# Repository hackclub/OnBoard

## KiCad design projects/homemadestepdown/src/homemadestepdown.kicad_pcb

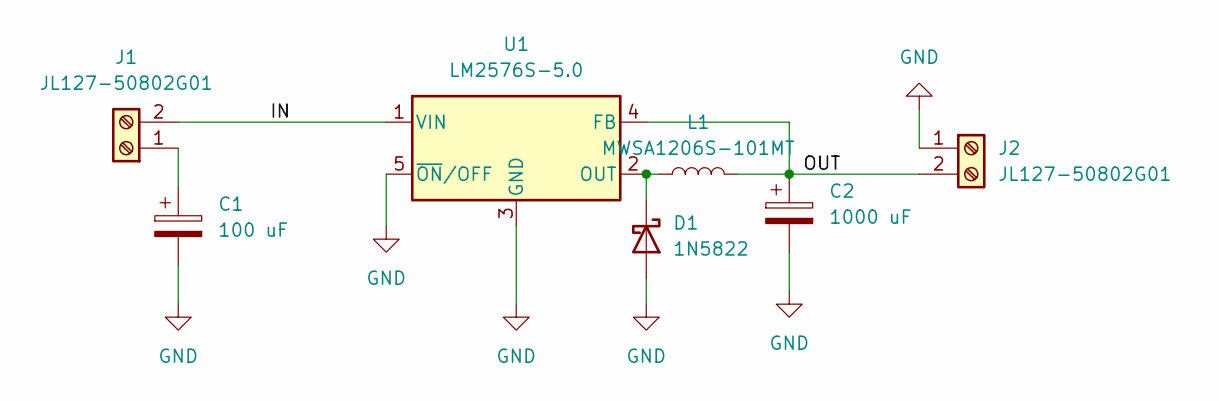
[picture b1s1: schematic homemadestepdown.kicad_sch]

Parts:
C1: 100 uF; CAP-SMD_BD8.0-L8.3-W8.3-FD; LCSC Part # C116241
C2: 1000 uF; CAP-TH_BD8.0-P3.50-D0.6-FD; LCSC Part # C311638
D1: 1N5822; D_DO-201AD_P15.24mm_Horizontal; LCSC Part # C2476
J1, J2: JL127-50802G01; CONN-TH_2P-P5.08_JL127-50802G01; LCSC Part # C409161
L1: MWSA1206S-101MT; IND-SMD_L13.4-W12.6; LCSC Part # C408533
U1: LM2576S-5.0; TO-263-5_TabPin3; LCSC Part # C2920854

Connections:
/IN: J1.2, U1.1 (VIN)
/OUT: C2.1, J2.2, L1.2, U1.4 (FB)
GND: C1.2, C2.2, D1.2 (A), J2.1, U1.3 (GND), U1.5 (~ON/OFF)
unnamed: D1.1 (K), L1.1, U1.2 (OUT)
unnamed: C1.1, J1.1

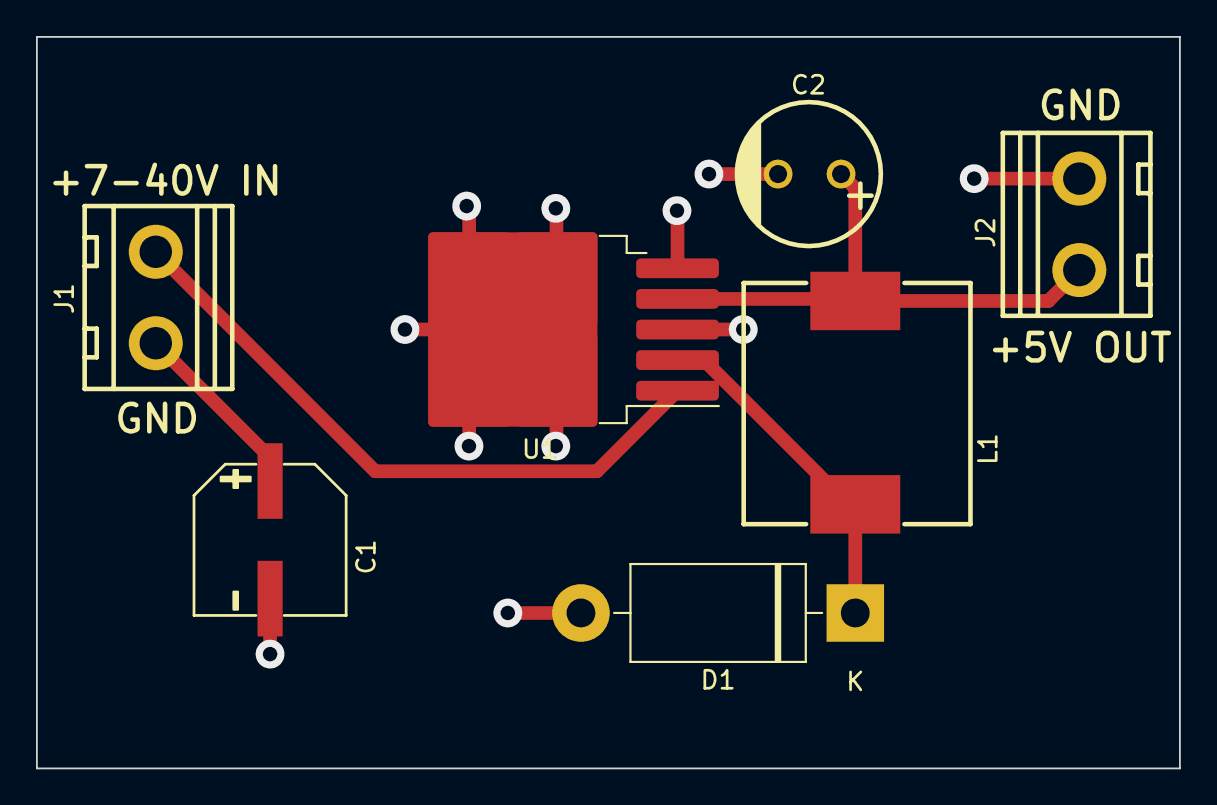
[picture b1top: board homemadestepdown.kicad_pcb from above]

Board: 2 copper layers, 63.5 x 40.6 mm, 7 parts (0 on the bottom side), 5 nets.

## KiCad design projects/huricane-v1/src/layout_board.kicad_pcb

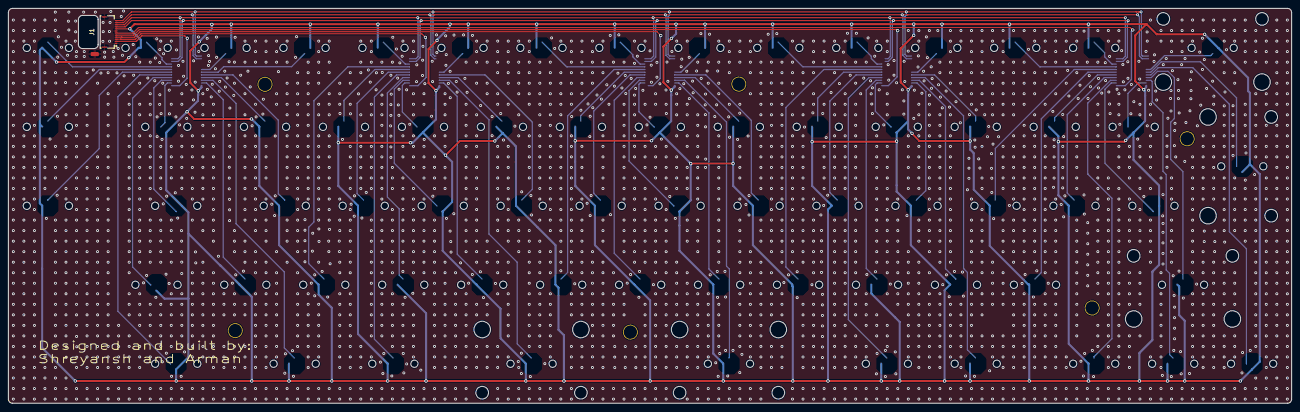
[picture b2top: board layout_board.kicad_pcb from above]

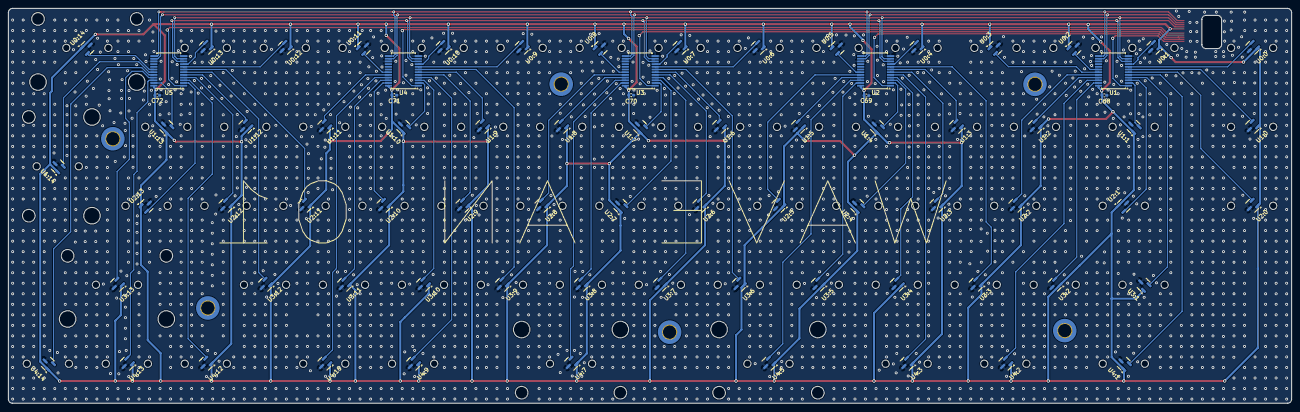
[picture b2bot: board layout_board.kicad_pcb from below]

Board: 2 copper layers, 309.6 x 95.2 mm, 78 parts (77 on the bottom side), 78 nets.

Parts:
C68, C69, C70, C71, C72: 100n; C_0402_1005Metric_Pad0.74x0.62mm_HandSolder
J1: HC-FPC-05-10-12RLTAG; FPC-SMD_12P-P0.50_HCTL_HC-FPC-05-10-12RLTAG
U0:0, U0:1, U0:2, U0:3, U0:4, U0:5, U0:6, U0:7, U0:8, U0:9, U0:10, U0:11, U0:12, U0:13, U0:14, U1:0, U1:1, U1:2, U1:3, U1:4, U1:5, U1:6, U1:7, U1:8, U1:9, U1:10, U1:11, U1:12, U1:13, U1:14, U2:0, U2:1, U2:2, U2:3, U2:4, U2:5, U2:6, U2:7, U2:8, U2:9, U2:10, U2:11, U2:12, U2:13, U3:1, U3:2, U3:3, U3:4, U3:5, U3:6, U3:7, U3:8, U3:9, U3:10, U3:11, U3:12, U3:13, U4:1, U4:2, U4:3, U4:5, U4:7, U4:9, U4:10, U4:12, U4:13, U4:14: GH39FKSW; SOT-23
U1, U2, U3, U4, U5: CD4067BPWR; SSOP-24_5.3x8.2mm_P0.65mm

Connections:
+3.3VA: C68.1, C69.1, C70.1, C71.1, C72.1, J1.8, U0:0.1 (VDD), U0:1.1 (VDD), U0:2.1 (VDD), U0:3.1 (VDD), U0:4.1 (VDD), U0:5.1 (VDD), U0:6.1 (VDD), U0:7.1 (VDD), U0:8.1 (VDD), U0:9.1 (VDD), U0:10.1 (VDD), U0:11.1 (VDD), U0:12.1 (VDD), U0:13.1 (VDD), U0:14.1 (VDD), U1.24 (VDD), U1:0.1 (VDD), U1:1.1 (VDD), U1:2.1 (VDD), U1:3.1 (VDD), U1:4.1 (VDD), U1:5.1 (VDD), U1:6.1 (VDD), U1:7.1 (VDD), U1:8.1 (VDD), U1:9.1 (VDD), U1:10.1 (VDD), U1:11.1 (VDD), U1:12.1 (VDD), U1:13.1 (VDD), U1:14.1 (VDD), U2.24 (VDD), U2:0.1 (VDD), U2:1.1 (VDD), U2:2.1 (VDD), U2:3.1 (VDD), U2:4.1 (VDD), U2:5.1 (VDD), U2:6.1 (VDD), U2:7.1 (VDD), U2:8.1 (VDD), U2:9.1 (VDD), U2:10.1 (VDD), U2:11.1 (VDD), U2:12.1 (VDD), U2:13.1 (VDD), U3.24 (VDD), U3:1.1 (VDD), U3:2.1 (VDD), U3:3.1 (VDD), U3:4.1 (VDD), U3:5.1 (VDD), U3:6.1 (VDD), U3:7.1 (VDD), U3:8.1 (VDD), U3:9.1 (VDD), U3:10.1 (VDD), U3:11.1 (VDD), U3:12.1 (VDD), U3:13.1 (VDD), U4.24 (VDD), U4:1.1 (VDD), U4:2.1 (VDD), U4:3.1 (VDD), U4:5.1 (VDD), U4:7.1 (VDD), U4:9.1 (VDD), U4:10.1 (VDD), U4:12.1 (VDD), U4:13.1 (VDD), U4:14.1 (VDD), U5.24 (VDD)
/ADC0: J1.2, U1.1 (COMMONOUT/IN)
/ADC1: J1.3, U2.1 (COMMONOUT/IN)
/ADC2: J1.4, U3.1 (COMMONOUT/IN)
/ADC3: J1.5, U4.1 (COMMONOUT/IN)
/ADC4: J1.6, U5.1 (COMMONOUT/IN)
/AMUX0:0: U0:1.2 (VOUT), U1.9 (0)
/AMUX0:1: U0:0.2 (VOUT), U1.8 (1)
/AMUX0:2: U1.7 (2), U1:0.2 (VOUT)
/AMUX0:3: U1.6 (3), U2:0.2 (VOUT)
/AMUX0:4: U1.5 (4), U4:1.2 (VOUT)
/AMUX0:5: U1.4 (5), U3:1.2 (VOUT)
/AMUX0:6: U1.3 (6), U2:1.2 (VOUT)
/AMUX0:7: U1.2 (7), U1:1.2 (VOUT)
/AMUX0:8: U1.23 (8), U3:2.2 (VOUT)
/AMUX0:9: U1.22 (9), U4:2.2 (VOUT)
/AMUX0:10: U1.21 (10), U1:2.2 (VOUT)
/AMUX0:11: U1.20 (11), U2:2.2 (VOUT)
/AMUX0:12: U0:3.2 (VOUT), U1.19 (12)
/AMUX0:13: U0:2.2 (VOUT), U1.18 (13)
/AMUX1:0: U0:4.2 (VOUT), U2.9 (0)
/AMUX1:1: U2.8 (1), U3:3.2 (VOUT)
/AMUX1:2: U1:3.2 (VOUT), U2.7 (2)
/AMUX1:3: U2.6 (3), U2:3.2 (VOUT)
/AMUX1:4: U2.5 (4), U4:3.2 (VOUT)
/AMUX1:5: U2.4 (5), U3:4.2 (VOUT)
/AMUX1:6: U2.3 (6), U2:4.2 (VOUT)
/AMUX1:7: U1:4.2 (VOUT), U2.2 (7)
/AMUX1:8: U2.23 (8), U3:5.2 (VOUT)
/AMUX1:9: U2.22 (9), U4:5.2 (VOUT)
/AMUX1:10: U1:5.2 (VOUT), U2.21 (10)
/AMUX1:11: U2.20 (11), U2:5.2 (VOUT)
/AMUX1:12: U0:5.2 (VOUT), U2.19 (12)
/AMUX2:0: U0:7.2 (VOUT), U3.9 (0)
/AMUX2:1: U0:6.2 (VOUT), U3.8 (1)
/AMUX2:2: U3.7 (2), U3:6.2 (VOUT)
/AMUX2:3: U1:6.2 (VOUT), U3.6 (3)
/AMUX2:4: U2:6.2 (VOUT), U3.5 (4)
/AMUX2:5: U3.4 (5), U3:7.2 (VOUT)
/AMUX2:6: U2:7.2 (VOUT), U3.3 (6)
/AMUX2:7: U1:7.2 (VOUT), U3.2 (7)
/AMUX2:8: U3.23 (8), U3:8.2 (VOUT)
/AMUX2:9: U3.22 (9), U4:7.2 (VOUT)
/AMUX2:10: U1:8.2 (VOUT), U3.21 (10)
/AMUX2:11: U2:8.2 (VOUT), U3.20 (11)
/AMUX2:12: U0:8.2 (VOUT), U3.19 (12)
/AMUX3:0: U0:10.2 (VOUT), U4.9 (0)
/AMUX3:1: U0:9.2 (VOUT), U4.8 (1)
/AMUX3:2: U3:9.2 (VOUT), U4.7 (2)
/AMUX3:3: U1:9.2 (VOUT), U4.6 (3)
/AMUX3:4: U2:9.2 (VOUT), U4.5 (4)
/AMUX3:5: U4.4 (5), U4:9.2 (VOUT)
/AMUX3:6: U3:10.2 (VOUT), U4.3 (6)
/AMUX3:7: U1:10.2 (VOUT), U4.2 (7)
/AMUX3:8: U2:10.2 (VOUT), U4.23 (8)
/AMUX3:9: U3:11.2 (VOUT), U4.22 (9)
/AMUX3:10: U4.21 (10), U4:10.2 (VOUT)
/AMUX3:11: U1:11.2 (VOUT), U4.20 (11)
/AMUX3:12: U0:11.2 (VOUT), U4.19 (12)
/AMUX4:0: U0:13.2 (VOUT), U5.9 (0)
/AMUX4:1: U0:12.2 (VOUT), U5.8 (1)
/AMUX4:2: U2:11.2 (VOUT), U5.7 (2)
/AMUX4:3: U3:12.2 (VOUT), U5.6 (3)
/AMUX4:4: U1:12.2 (VOUT), U5.5 (4)
/AMUX4:5: U2:12.2 (VOUT), U5.4 (5)
/AMUX4:6: U4:12.2 (VOUT), U5.3 (6)
/AMUX4:7: U2:13.2 (VOUT), U5.2 (7)
/AMUX4:8: U1:13.2 (VOUT), U5.23 (8)
/AMUX4:9: U4:13.2 (VOUT), U5.22 (9)
/AMUX4:10: U3:13.2 (VOUT), U5.21 (10)
/AMUX4:11: U4:14.2 (VOUT), U5.20 (11)
/AMUX4:12: U1:14.2 (VOUT), U5.19 (12)
/AMUX4:13: U0:14.2 (VOUT), U5.18 (13)
/SELECT0: J1.9, U1.10 (A), U2.10 (A), U3.10 (A), U4.10 (A), U5.10 (A)
/SELECT1: J1.10, U1.11 (B), U2.11 (B), U3.11 (B), U4.11 (B), U5.11 (B)
/SELECT2: J1.11, U1.14 (C), U2.14 (C), U3.14 (C), U4.14 (C), U5.14 (C)
/SELECT3: J1.12, U1.13 (D), U2.13 (D), U3.13 (D), U4.13 (D), U5.13 (D)
GND: C68.2, C69.2, C70.2, C71.2, C72.2, J1.1, J1.7, J1.13, J1.14, U0:0.3 (GND), U0:1.3 (GND), U0:2.3 (GND), U0:3.3 (GND), U0:4.3 (GND), U0:5.3 (GND), U0:6.3 (GND), U0:7.3 (GND), U0:8.3 (GND), U0:9.3 (GND), U0:10.3 (GND), U0:11.3 (GND), U0:12.3 (GND), U0:13.3 (GND), U0:14.3 (GND), U1.12 (VSS), U1.15 (INHIBT), U1:0.3 (GND), U1:1.3 (GND), U1:2.3 (GND), U1:3.3 (GND), U1:4.3 (GND), U1:5.3 (GND), U1:6.3 (GND), U1:7.3 (GND), U1:8.3 (GND), U1:9.3 (GND), U1:10.3 (GND), U1:11.3 (GND), U1:12.3 (GND), U1:13.3 (GND), U1:14.3 (GND), U2.12 (VSS), U2.15 (INHIBT), U2:0.3 (GND), U2:1.3 (GND), U2:2.3 (GND), U2:3.3 (GND), U2:4.3 (GND), U2:5.3 (GND), U2:6.3 (GND), U2:7.3 (GND), U2:8.3 (GND), U2:9.3 (GND), U2:10.3 (GND), U2:11.3 (GND), U2:12.3 (GND), U2:13.3 (GND), U3.12 (VSS), U3.15 (INHIBT), U3:1.3 (GND), U3:2.3 (GND), U3:3.3 (GND), U3:4.3 (GND), U3:5.3 (GND), U3:6.3 (GND), U3:7.3 (GND), U3:8.3 (GND), U3:9.3 (GND), U3:10.3 (GND), U3:11.3 (GND), U3:12.3 (GND), U3:13.3 (GND), U4.12 (VSS), U4.15 (INHIBT), U4:1.3 (GND), U4:2.3 (GND), U4:3.3 (GND), U4:5.3 (GND), U4:7.3 (GND), U4:9.3 (GND), U4:10.3 (GND), U4:12.3 (GND), U4:13.3 (GND), U4:14.3 (GND), U5.12 (VSS), U5.15 (INHIBT)

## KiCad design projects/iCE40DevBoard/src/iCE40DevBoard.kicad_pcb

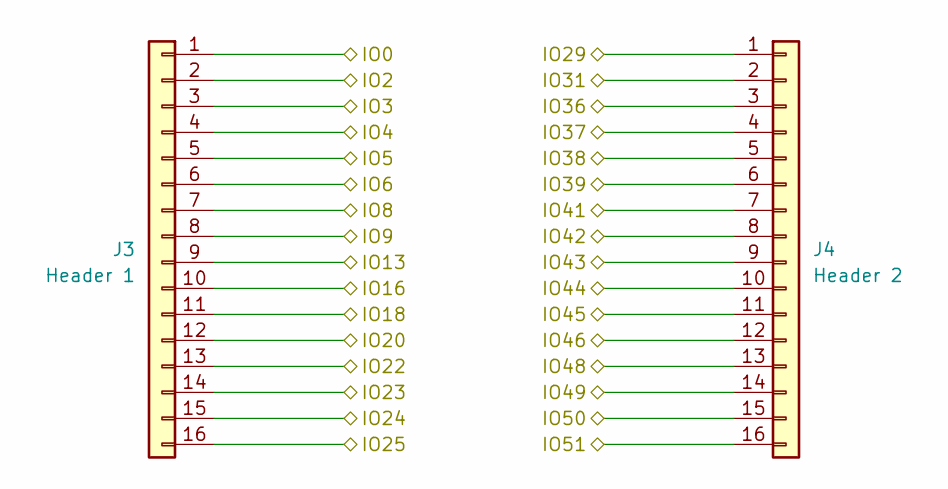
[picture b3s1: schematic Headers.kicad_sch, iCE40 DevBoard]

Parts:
J3: Header 1; PinHeader_1x16_P2.54mm_Vertical
J4: Header 2; PinHeader_1x16_P2.54mm_Vertical

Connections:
/FPGA/IO0: J3.1; also elsewhere on the board
/FPGA/IO2: J3.2; also elsewhere on the board
/FPGA/IO3: J3.3; also elsewhere on the board
/FPGA/IO4: J3.4; also elsewhere on the board
/FPGA/IO5: J3.5; also elsewhere on the board
/FPGA/IO6: J3.6; also elsewhere on the board
/FPGA/IO8: J3.7; also elsewhere on the board
/FPGA/IO9: J3.8; also elsewhere on the board
/FPGA/IO13: J3.9; also elsewhere on the board
/FPGA/IO16: J3.10; also elsewhere on the board
/FPGA/IO18: J3.11; also elsewhere on the board
/FPGA/IO20: J3.12; also elsewhere on the board
/FPGA/IO22: J3.13; also elsewhere on the board
/FPGA/IO23: J3.14; also elsewhere on the board
/FPGA/IO24: J3.15; also elsewhere on the board
/FPGA/IO25: J3.16; also elsewhere on the board
/FPGA/IO29: J4.1; also elsewhere on the board
/FPGA/IO31: J4.2; also elsewhere on the board
/FPGA/IO36: J4.3; also elsewhere on the board
/FPGA/IO37: J4.4; also elsewhere on the board
/FPGA/IO38: J4.5; also elsewhere on the board
/FPGA/IO39: J4.6; also elsewhere on the board
/FPGA/IO41: J4.7; also elsewhere on the board
/FPGA/IO42: J4.8; also elsewhere on the board
/FPGA/IO43: J4.9; also elsewhere on the board
/FPGA/IO44: J4.10; also elsewhere on the board
/FPGA/IO45: J4.11; also elsewhere on the board
/FPGA/IO46: J4.12; also elsewhere on the board
/FPGA/IO48: J4.13; also elsewhere on the board
/FPGA/IO49: J4.14; also elsewhere on the board
/FPGA/IO50: J4.15; also elsewhere on the board
/FPGA/IO51: J4.16; also elsewhere on the board

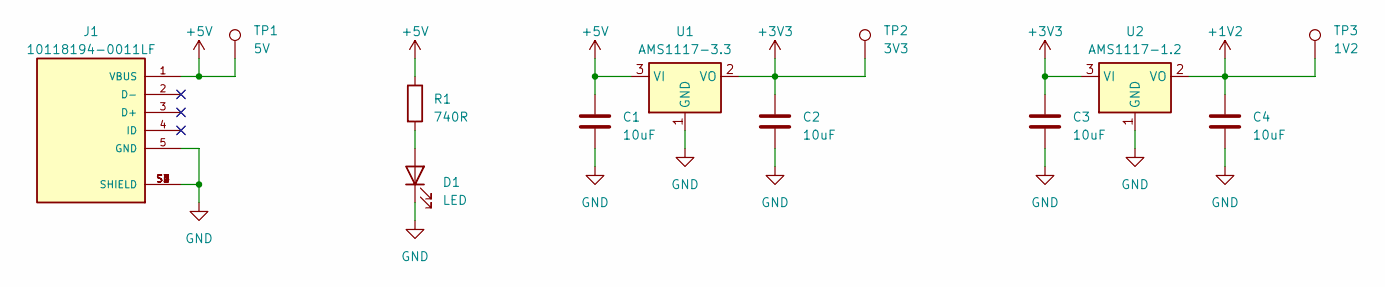
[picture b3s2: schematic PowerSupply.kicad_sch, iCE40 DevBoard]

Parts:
C1, C2, C3, C4: 10uF; C_0603_1608Metric
D1: LED; LED_0805_2012Metric
J1: 10118194-0011LF; AMPHENOL_10118194-0011LF; PARTREV D
R1: 740R; R_0603_1608Metric
TP1: 5V; TestPoint_Pad_D1.0mm
TP2: 3V3; TestPoint_Pad_D1.0mm
TP3: 1V2; TestPoint_Pad_D1.0mm
U1: AMS1117-3.3; SOT-223-3_TabPin2
U2: AMS1117-1.2; SOT-223-3_TabPin2

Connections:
+1V2: C4.1, TP3.1, U2.2 (VO); also elsewhere on the board
+3V3: C2.1, C3.1, TP2.1, U1.2 (VO), U2.3 (VI); also elsewhere on the board
+5V: C1.1, J1.1 (VBUS), R1.1, TP1.1, U1.3 (VI); also elsewhere on the board
GND: C1.2, C2.2, C3.2, C4.2, D1.1 (K), J1.5 (GND), J1.S1 (SHIELD), J1.S2 (SHIELD), J1.S3 (SHIELD), J1.S4 (SHIELD), J1.S5 (SHIELD), J1.S6 (SHIELD), U1.1 (GND), U2.1 (GND); also elsewhere on the board
unnamed: D1.2 (A), R1.2

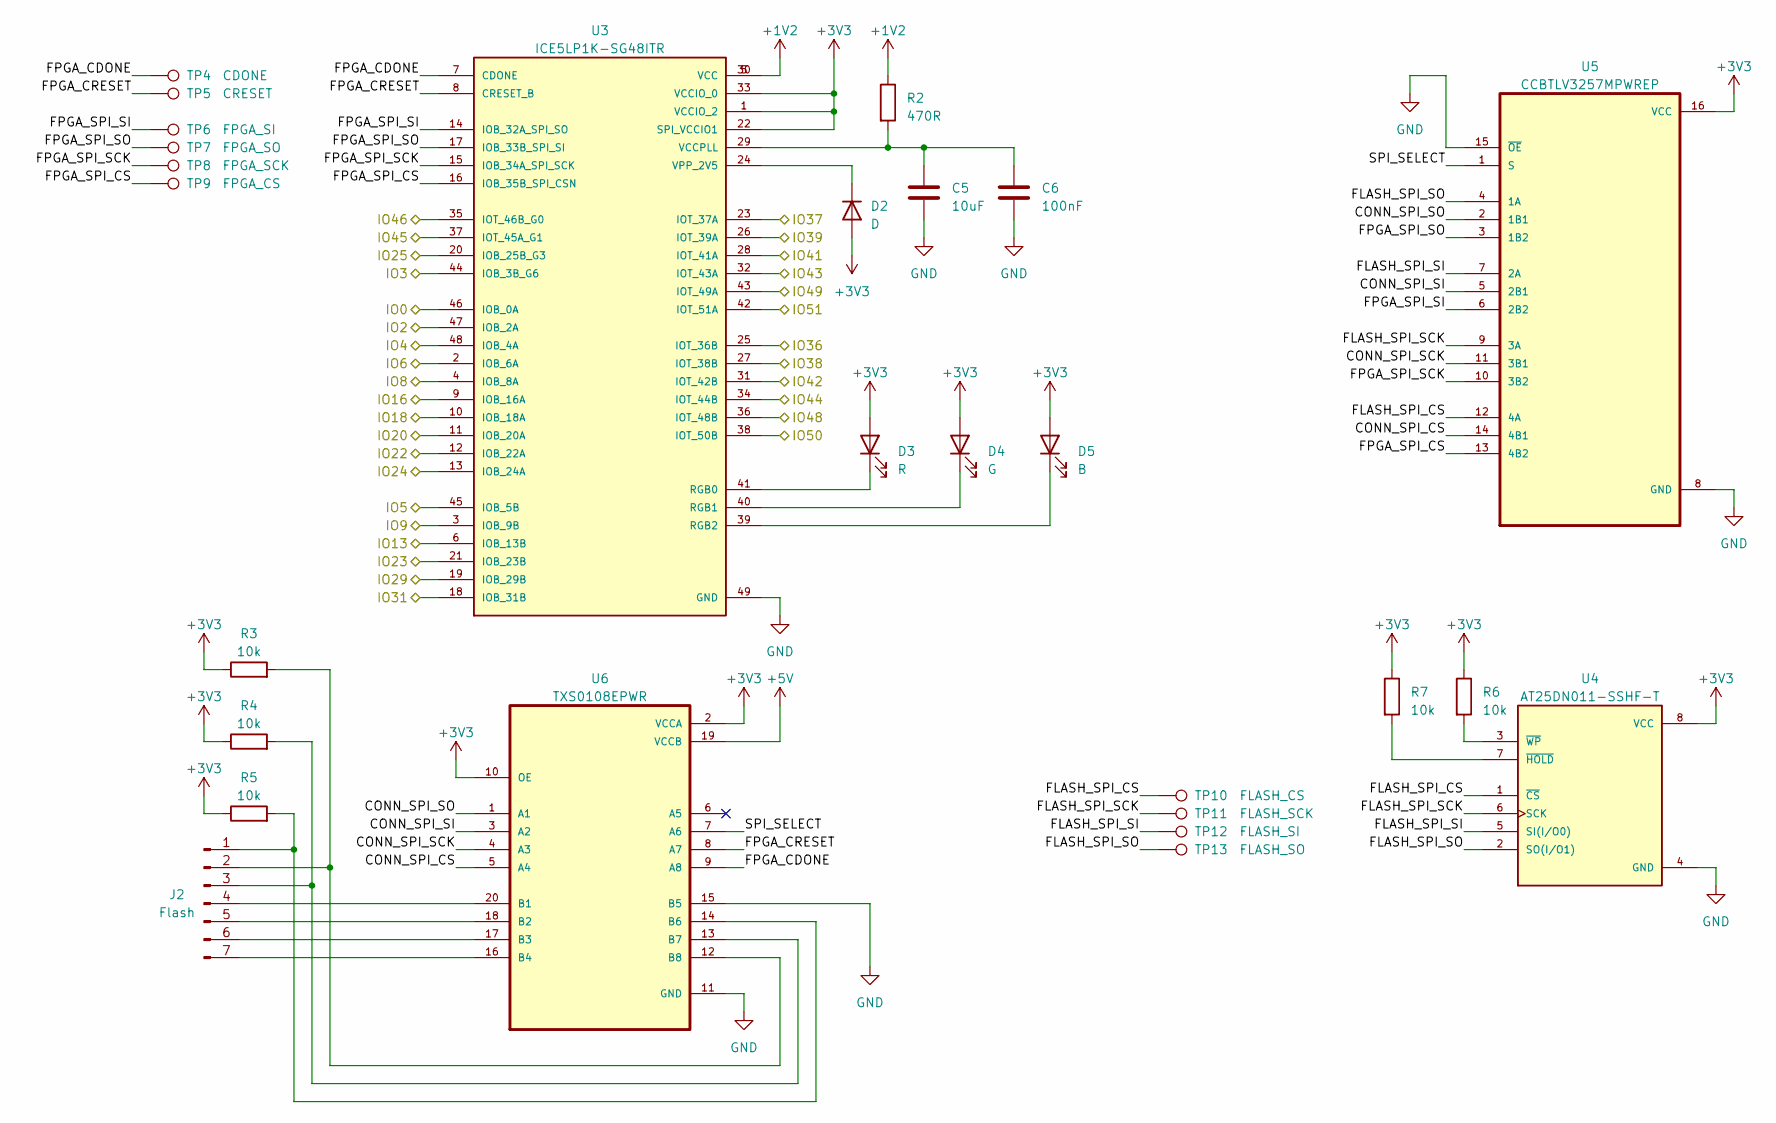
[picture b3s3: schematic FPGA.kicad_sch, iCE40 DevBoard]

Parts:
C5: 10uF; C_0603_1608Metric
C6: 100nF; C_0603_1608Metric
D2: D; D_0603_1608Metric
D3: R; LED_0805_2012Metric
D4: G; LED_0805_2012Metric
D5: B; LED_0805_2012Metric
J2: Flash; PinHeader_1x07_P2.54mm_Vertical
R2: 470R; R_0603_1608Metric
R3, R4, R5, R6, R7: 10k; R_0603_1608Metric
TP4: CDONE; TestPoint_Pad_D1.0mm
TP5: CRESET; TestPoint_Pad_D1.0mm
TP6: FPGA_SI; TestPoint_Pad_D1.0mm
TP7: FPGA_SO; TestPoint_Pad_D1.0mm
TP8: FPGA_SCK; TestPoint_Pad_D1.0mm
TP9: FPGA_CS; TestPoint_Pad_D1.0mm
TP10: FLASH_CS; TestPoint_Pad_D1.0mm
TP11: FLASH_SCK; TestPoint_Pad_D1.0mm
TP12: FLASH_SI; TestPoint_Pad_D1.0mm
TP13: FLASH_SO; TestPoint_Pad_D1.0mm
U3: ICE5LP1K-SG48ITR; QFN50P700X700X100-49N
U4: AT25DN011-SSHF-T; SOIC127P599X175-8N; PARTREV G
U5: CCBTLV3257MPWREP; SOP65P640X120-16N
U6: TXS0108EPWR; SOP65P640X120-20N

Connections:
+1V2: R2.1, U3.5 (VCC), U3.30 (VCC); also elsewhere on the board
+3V3: D2.2 (A), D3.2 (A), D4.2 (A), D5.2 (A), R3.1, R4.1, R5.1, R6.1, R7.1, U3.1 (VCCIO_2), U3.22 (SPI_VCCIO1), U3.33 (VCCIO_0), U4.8 (VCC), U5.16 (VCC), U6.2 (VCCA), U6.10 (OE); also elsewhere on the board
+5V: U6.19 (VCCB); also elsewhere on the board
/FPGA/CONN_SPI_CS: U5.14 (4B1), U6.5 (A4)
/FPGA/CONN_SPI_SCK: U5.11 (3B1), U6.4 (A3)
/FPGA/CONN_SPI_SI: U5.5 (2B1), U6.3 (A2)
/FPGA/CONN_SPI_SO: U5.2 (1B1), U6.1 (A1)
/FPGA/FLASH_SPI_CS: TP10.1, U4.1 (~CS), U5.12 (4A)
/FPGA/FLASH_SPI_SCK: TP11.1, U4.6 (SCK), U5.9 (3A)
/FPGA/FLASH_SPI_SI: TP12.1, U4.5 (SI(I/O0)), U5.7 (2A)
/FPGA/FLASH_SPI_SO: TP13.1, U4.2 (SO(I/O1)), U5.4 (1A)
/FPGA/FPGA_CDONE: TP4.1, U3.7 (CDONE), U6.9 (A8)
/FPGA/FPGA_CRESET: TP5.1, U3.8 (CRESET_B), U6.8 (A7)
/FPGA/FPGA_SPI_CS: TP9.1, U3.16 (IOB_35B_SPI_CSN), U5.13 (4B2)
/FPGA/FPGA_SPI_SCK: TP8.1, U3.15 (IOB_34A_SPI_SCK), U5.10 (3B2)
/FPGA/FPGA_SPI_SI: TP6.1, U3.14 (IOB_32A_SPI_SO), U5.6 (2B2)
/FPGA/FPGA_SPI_SO: TP7.1, U3.17 (IOB_33B_SPI_SI), U5.3 (1B2)
/FPGA/IO0: U3.46 (IOB_0A); also elsewhere on the board
/FPGA/IO2: U3.47 (IOB_2A); also elsewhere on the board
/FPGA/IO3: U3.44 (IOB_3B_G6); also elsewhere on the board
/FPGA/IO4: U3.48 (IOB_4A); also elsewhere on the board
/FPGA/IO5: U3.45 (IOB_5B); also elsewhere on the board
/FPGA/IO6: U3.2 (IOB_6A); also elsewhere on the board
/FPGA/IO8: U3.4 (IOB_8A); also elsewhere on the board
/FPGA/IO9: U3.3 (IOB_9B); also elsewhere on the board
/FPGA/IO13: U3.6 (IOB_13B); also elsewhere on the board
/FPGA/IO16: U3.9 (IOB_16A); also elsewhere on the board
/FPGA/IO18: U3.10 (IOB_18A); also elsewhere on the board
/FPGA/IO20: U3.11 (IOB_20A); also elsewhere on the board
/FPGA/IO22: U3.12 (IOB_22A); also elsewhere on the board
/FPGA/IO23: U3.21 (IOB_23B); also elsewhere on the board
/FPGA/IO24: U3.13 (IOB_24A); also elsewhere on the board
/FPGA/IO25: U3.20 (IOB_25B_G3); also elsewhere on the board
/FPGA/IO29: U3.19 (IOB_29B); also elsewhere on the board
/FPGA/IO31: U3.18 (IOB_31B); also elsewhere on the board
/FPGA/IO36: U3.25 (IOT_36B); also elsewhere on the board
/FPGA/IO37: U3.23 (IOT_37A); also elsewhere on the board
/FPGA/IO38: U3.27 (IOT_38B); also elsewhere on the board
/FPGA/IO39: U3.26 (IOT_39A); also elsewhere on the board
/FPGA/IO41: U3.28 (IOT_41A); also elsewhere on the board
/FPGA/IO42: U3.31 (IOT_42B); also elsewhere on the board
/FPGA/IO43: U3.32 (IOT_43A); also elsewhere on the board
/FPGA/IO44: U3.34 (IOT_44B); also elsewhere on the board
/FPGA/IO45: U3.37 (IOT_45A_G1); also elsewhere on the board
/FPGA/IO46: U3.35 (IOT_46B_G0); also elsewhere on the board
/FPGA/IO48: U3.36 (IOT_48B); also elsewhere on the board
/FPGA/IO49: U3.43 (IOT_49A); also elsewhere on the board
/FPGA/IO50: U3.38 (IOT_50B); also elsewhere on the board
/FPGA/IO51: U3.42 (IOT_51A); also elsewhere on the board
/FPGA/SPI_SELECT: U5.1 (S), U6.7 (A6)
GND: C5.2, C6.2, U3.49 (GND), U4.4 (GND), U5.8 (GND), U5.15 (~OE), U6.11 (GND), U6.15 (B5); also elsewhere on the board
unnamed: D2.1 (K), U3.24 (VPP_2V5)
unnamed: D3.1 (K), U3.41 (RGB0)
unnamed: D4.1 (K), U3.40 (RGB1)
unnamed: D5.1 (K), U3.39 (RGB2)
unnamed: J2.1, R5.2, U6.14 (B6)
unnamed: J2.2, R3.2, U6.12 (B8)
unnamed: J2.3, R4.2, U6.13 (B7)
unnamed: J2.4, U6.20 (B1)
unnamed: J2.5, U6.18 (B2)
unnamed: J2.6, U6.17 (B3)
unnamed: J2.7, U6.16 (B4)
unnamed: C5.1, C6.1, R2.2, U3.29 (VCCPLL)
unnamed: R7.2, U4.7 (~HOLD)
unnamed: R6.2, U4.3 (~WP)

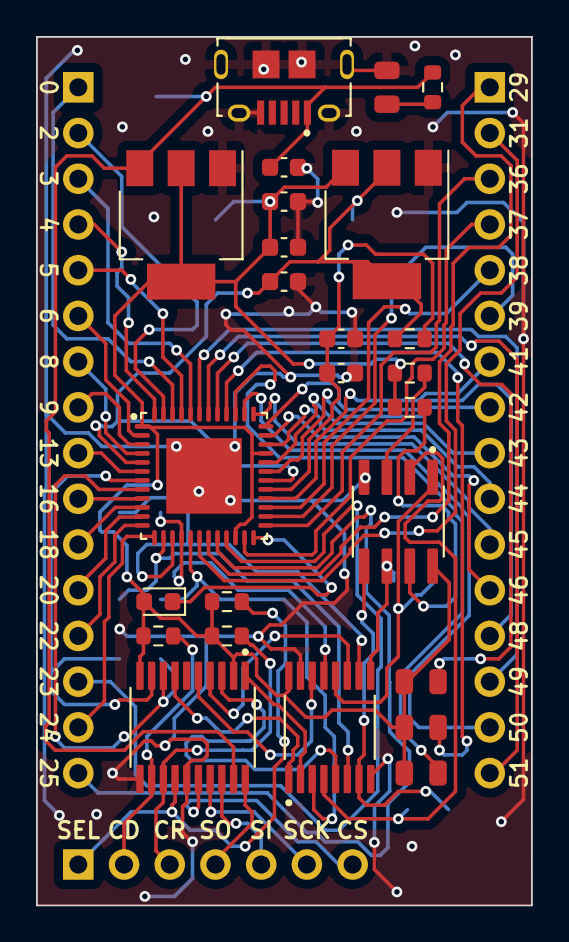
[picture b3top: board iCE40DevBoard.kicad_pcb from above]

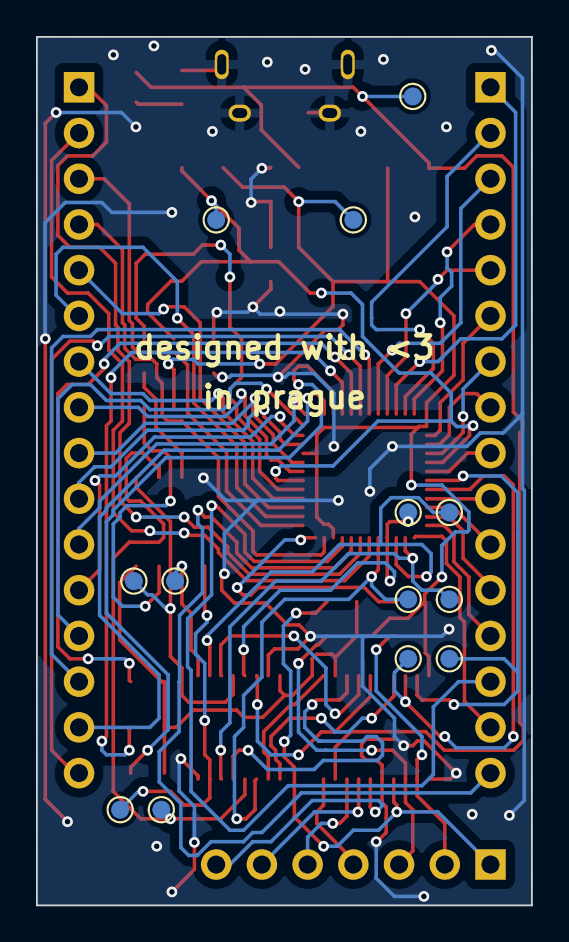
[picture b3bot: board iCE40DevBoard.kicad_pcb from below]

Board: 2 copper layers, 27.5 x 48.2 mm, 41 parts (13 on the bottom side), 66 nets.

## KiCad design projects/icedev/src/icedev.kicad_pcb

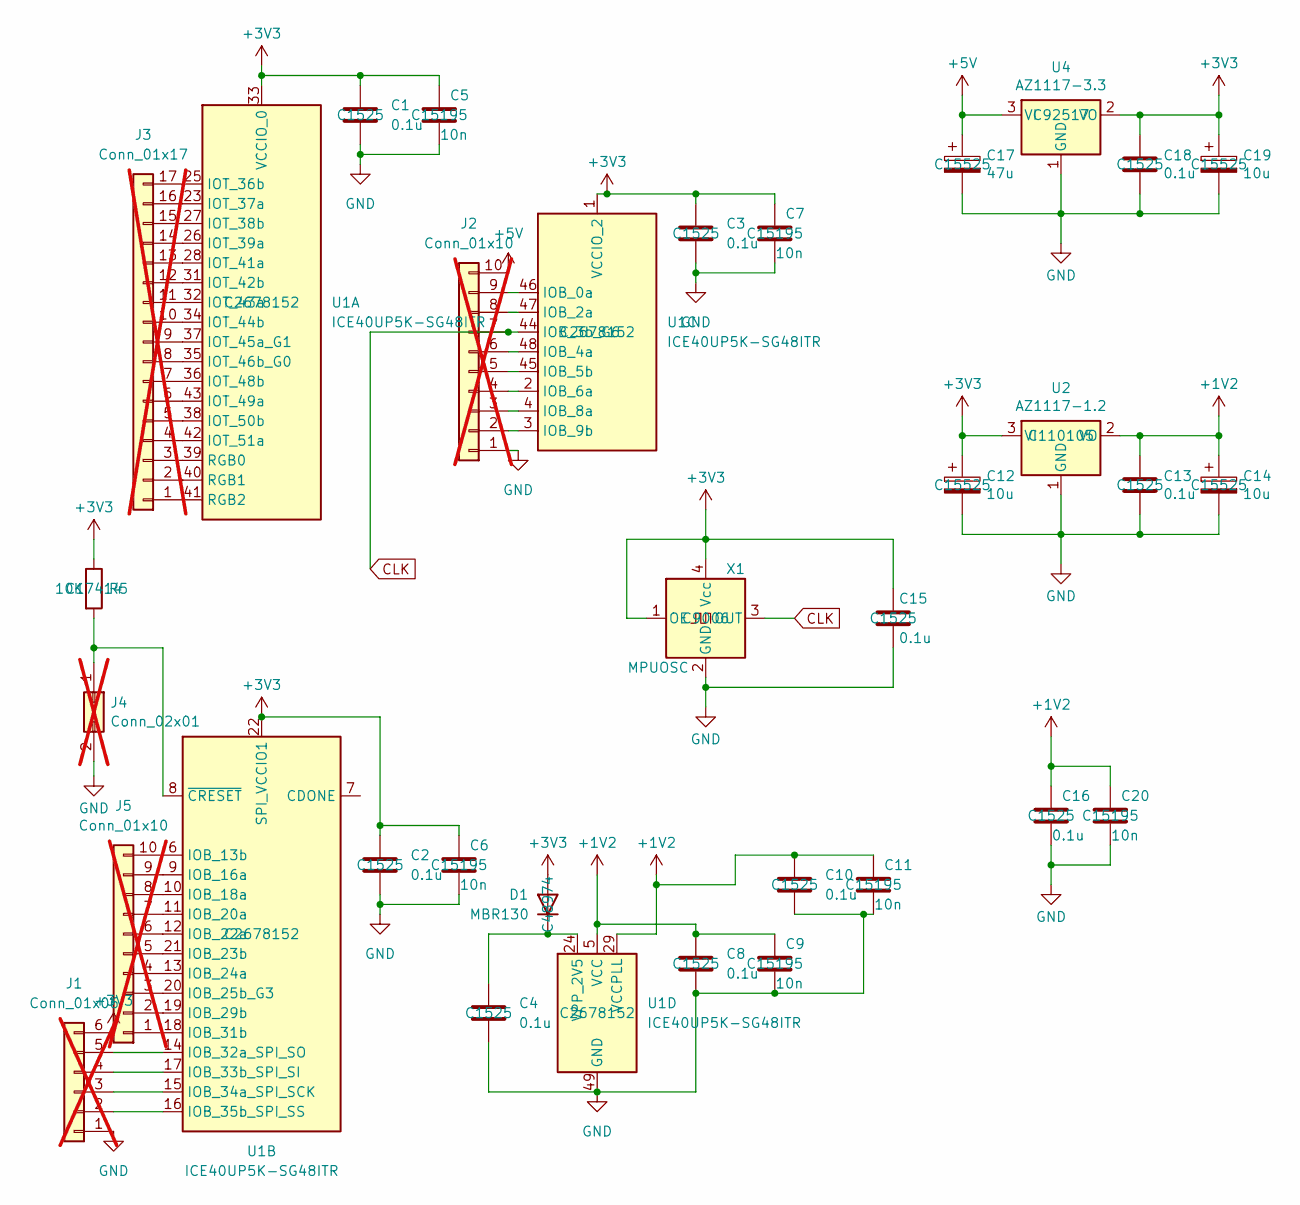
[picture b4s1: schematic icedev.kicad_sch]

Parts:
C1, C2, C3, C4, C8, C10, C13, C15, C16, C18: 0.1u; C_0402_1005Metric; JLCPCB Part # C1525
C5, C6, C7, C9, C11, C20: 10n; C_0402_1005Metric; JLCPCB Part # C15195
C12, C14, C19: 10u; C_0402_1005Metric; JLCPCB Part # C15525
C17: 47u; C_0402_1005Metric; JLCPCB Part # C15525
D1: MBR130; D_SOD-123; JLCPCB Part # C48974
J1: Conn_01x06; PinHeader_1x06_P2.54mm_Vertical; not fitted
J2, J5: Conn_01x10; PinHeader_1x10_P2.54mm_Vertical; not fitted
J3: Conn_01x17; PinHeader_1x17_P2.54mm_Vertical; not fitted
J4: Conn_02x01; PinHeader_2x01_P2.54mm_Vertical; not fitted
R5: 10K; R_0805_2012Metric; JLCPCB Part # C17414
U1: ICE40UP5K-SG48ITR; QFN-48-1EP_7x7mm_P0.5mm_EP5.6x5.6mm; JLCPCB Part # C2678152
U2: AZ1117-1.2; SOT-223-3_TabPin2; JLCPCB Part # C110105
U4: AZ1117-3.3; SOT-223-3_TabPin2; JLCPCB Part # C92517
X1: MPUOSC; Oscillator_SMD_SeikoEpson_SG8002LB-4Pin_5.0x3.2mm; JLCPCB Part # C9006

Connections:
+1V2: C8.1, C9.1, C10.1, C11.1, C13.1, C14.1, C16.1, C20.1, U1.5 (VCC), U1.29 (VCCPLL), U1.30 (VCC), U2.2 (VO)
+3V3: C1.1, C2.1, C3.1, C5.1, C6.1, C7.1, C12.1, C15.1, C18.1, C19.1, D1.2 (A), J1.6, R5.1, U1.1 (VCCIO_2), U1.22 (SPI_VCCIO1), U1.33 (VCCIO_0), U2.3 (VI), U4.2 (VO), X1.1 (OE), X1.4 (Vcc)
+5V: C17.1, J2.10, U4.3 (VI)
CLK: J2.7, U1.44 (IOB_3b_G6), X1.3 (OUT)
GND: C1.2, C2.2, C3.2, C4.2, C5.2, C6.2, C7.2, C8.2, C9.2, C10.2, C11.2, C12.2, C13.2, C14.2, C15.2, C16.2, C17.2, C18.2, C19.2, C20.2, J1.1, J2.1, J4.2, U1.49 (GND), U2.1 (GND), U4.1 (GND), X1.2 (GND)
unnamed: C4.1, D1.1 (K), U1.24 (VPP_2V5)
unnamed: J1.2, U1.16 (IOB_35b_SPI_SS)
unnamed: J1.3, U1.15 (IOB_34a_SPI_SCK)
unnamed: J1.4, U1.17 (IOB_33b_SPI_SI)
unnamed: J1.5, U1.14 (IOB_32a_SPI_SO)
unnamed: J2.2, U1.3 (IOB_9b)
unnamed: J2.3, U1.4 (IOB_8a)
unnamed: J2.4, U1.2 (IOB_6a)
unnamed: J2.5, U1.45 (IOB_5b)
unnamed: J2.6, U1.48 (IOB_4a)
unnamed: J2.8, U1.47 (IOB_2a)
unnamed: J2.9, U1.46 (IOB_0a)
unnamed: J3.1, U1.41 (RGB2)
unnamed: J3.2, U1.40 (RGB1)
unnamed: J3.3, U1.39 (RGB0)
unnamed: J3.4, U1.42 (IOT_51a)
unnamed: J3.5, U1.38 (IOT_50b)
unnamed: J3.6, U1.43 (IOT_49a)
unnamed: J3.7, U1.36 (IOT_48b)
unnamed: J3.8, U1.35 (IOT_46b_G0)
unnamed: J3.9, U1.37 (IOT_45a_G1)
unnamed: J3.10, U1.34 (IOT_44b)
unnamed: J3.11, U1.32 (IOT_43a)
unnamed: J3.12, U1.31 (IOT_42b)
unnamed: J3.13, U1.28 (IOT_41a)
unnamed: J3.14, U1.26 (IOT_39a)
unnamed: J3.15, U1.27 (IOT_38b)
unnamed: J3.16, U1.23 (IOT_37a)
unnamed: J3.17, U1.25 (IOT_36b)
unnamed: J4.1, R5.2, U1.8 (~CRESET)
unnamed: J5.1, U1.18 (IOB_31b)
unnamed: J5.2, U1.19 (IOB_29b)
unnamed: J5.3, U1.20 (IOB_25b_G3)
unnamed: J5.4, U1.13 (IOB_24a)
unnamed: J5.5, U1.21 (IOB_23b)
unnamed: J5.6, U1.12 (IOB_22a)
unnamed: J5.7, U1.11 (IOB_20a)
unnamed: J5.8, U1.10 (IOB_18a)
unnamed: J5.9, U1.9 (IOB_16a)
unnamed: J5.10, U1.6 (IOB_13b)

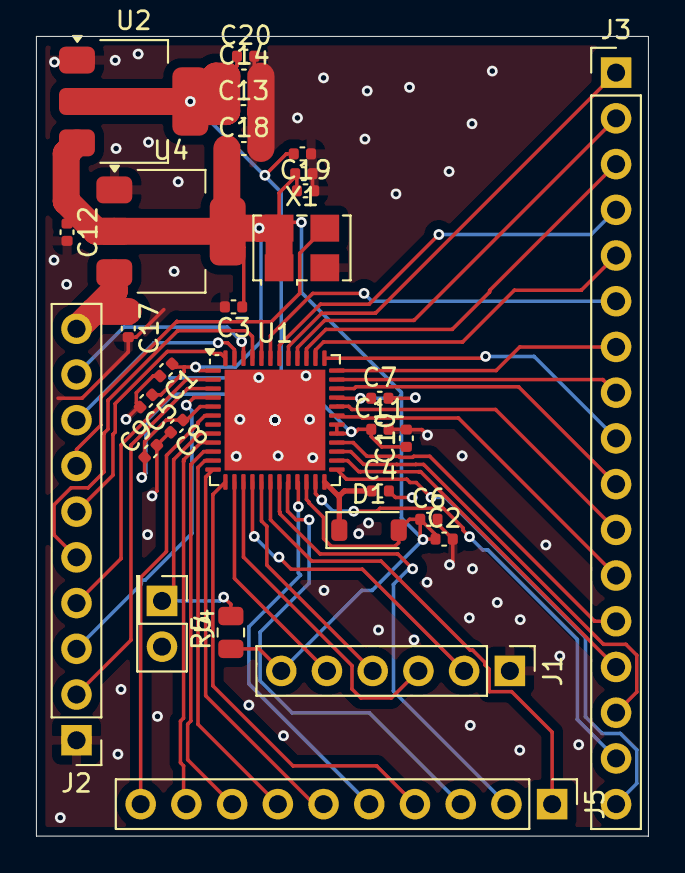
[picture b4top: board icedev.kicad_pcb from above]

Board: 2 copper layers, 34.0 x 44.4 mm, 31 parts (0 on the bottom side), 45 nets.

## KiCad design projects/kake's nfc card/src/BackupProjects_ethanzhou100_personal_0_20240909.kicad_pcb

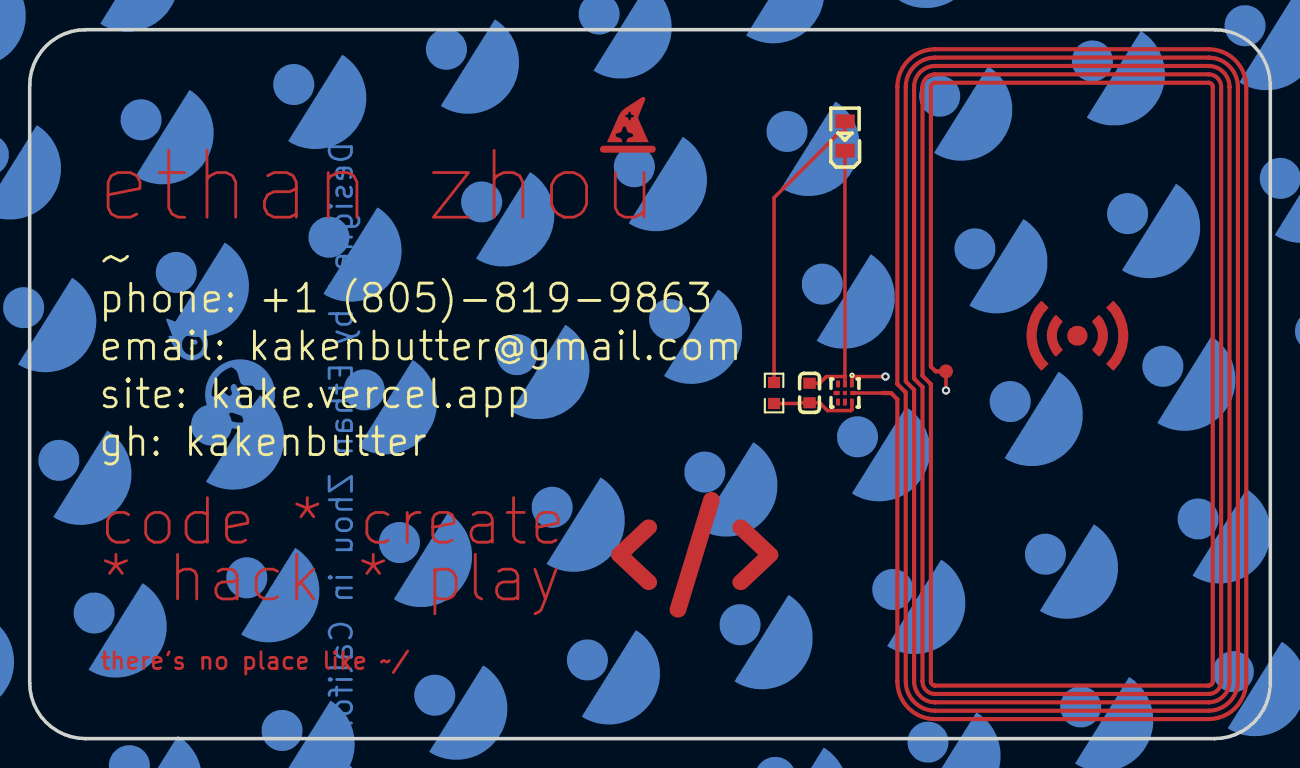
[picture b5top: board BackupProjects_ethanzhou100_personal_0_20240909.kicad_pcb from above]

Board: 4 copper layers, 88.9 x 50.8 mm, 5 parts (0 on the bottom side), 5 nets.

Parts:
1: 25X48MM_NFC_ANTENNA
CAPACITOR: 220nF; C0603
LED: 17-21SUYC/TR8; LED0805-R-RD
NFC: NT3H2111W0FHKH; XQFN-8_L1.6-W1.6-P0.50-BL
RESISTOR: 47Ω; R0603

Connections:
LED1_1: LED.1, RESISTOR.1
U1_1: 1.P$2, NFC.1
U1_2: CAPACITOR.1, LED.2, NFC.2
U1_7: CAPACITOR.2, NFC.7, RESISTOR.2
U1_8: 1.P$1, NFC.8

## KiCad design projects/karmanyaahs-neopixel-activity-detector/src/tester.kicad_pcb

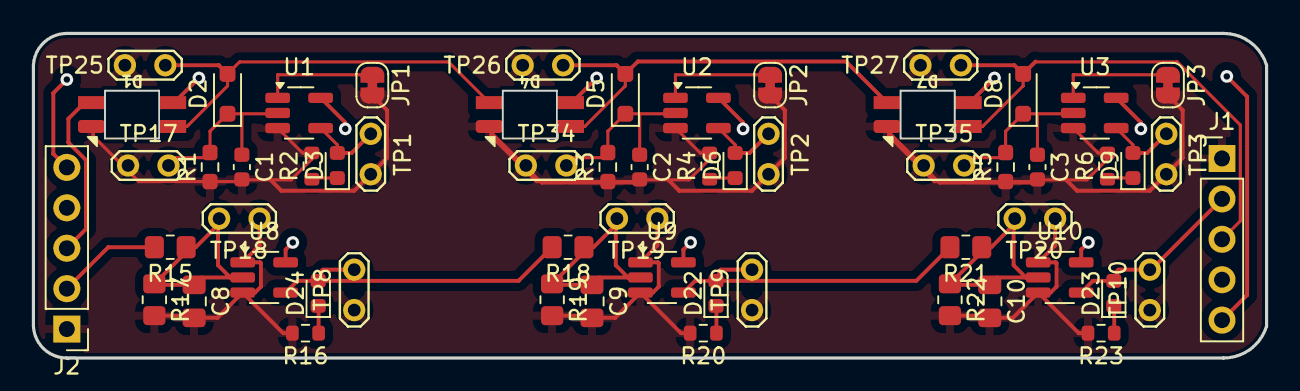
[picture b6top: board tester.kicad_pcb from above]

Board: 2 copper layers, 77.5 x 20.4 mm, 59 parts (0 on the bottom side), 29 nets.

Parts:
C1, C2, C3: 1u 50V; C_0603_1608Metric
C8, C9, C10: 1u 50V; C_0805_2012Metric_Pad1.18x1.45mm_HandSolder
D1, D4, D7: sk6812-mini-e; SK6812-MINI-E
D2, D5, D8: 1N4148WS; D_SOD-323_HandSoldering
D3, D6, D9: R; LED_0603_1608Metric
D22, D23, D24: Red; LED_0603_1608Metric
J1: Out; PinHeader_1x05_P2.54mm_Vertical
J2: In; PinHeader_1x05_P2.54mm_Vertical
JP1, JP2, JP3: SolderJumper_2_Bridged; SolderJumper-2_P1.3mm_Bridged_RoundedPad1.0x1.5mm
R1, R3, R5: 100k; R_0603_1608Metric_Pad0.98x0.95mm_HandSolder
R2, R4, R6: 310R; R_0603_1608Metric
R15, R18, R21: 100k; R_0805_2012Metric_Pad1.20x1.40mm_HandSolder
R16, R20, R23: 300; R_0603_1608Metric
R17, R19, R22: R; R_0805_2012Metric_Pad1.20x1.40mm_HandSolder
TP1, TP2, TP3, TP8, TP9, TP10, TP17, TP18, TP19, TP20, TP25, TP26, TP27, TP34, TP35: TestPoint_2Pole; TestPoint_2Pads_Pitch2.54mm_Drill0.8mm
U1, U2, U3, U8, U9, U10: 74LVC1G125; SOT-23-5_HandSoldering

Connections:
+3.3V: J1.4, J2.4, U1.5 (VCC), U2.5 (VCC), U3.5 (VCC), U8.5 (VCC), U9.5 (VCC), U10.5 (VCC)
+5V: D1.1 (VDD), D4.1 (VDD), D7.1 (VDD), J1.5, J2.5
/LED_BASED_RESET0/DIN: D1.4 (DIN), J2.3
/LED_BASED_RESET0/DOUT: D1.2 (DOUT), D2.2 (A), D4.4 (DIN), TP25.2
/LED_BASED_RESET1/DOUT: D4.2 (DOUT), D5.2 (A), D7.4 (DIN), TP26.2
/LED_BASED_RESET2/DOUT: D7.2 (DOUT), D8.2 (A), J1.3, TP27.2
/Time Based0/DIN: J2.2, R15.2
/Time Based0/DOUT: D24.2 (A), R18.2, TP8.2, U8.4
/Time Based1/DOUT: D22.2 (A), R21.2, TP9.2, U9.4
/Time Based2/DOUT: D23.2 (A), J1.2, TP10.2, U10.4
GND: C1.2, C2.2, C3.2, C8.2, C9.2, C10.2, D1.3 (VSS), D4.3 (VSS), D7.3 (VSS), J1.1, J2.1, JP1.2 (B), JP2.2 (B), JP3.2 (B), R1.1, R2.2, R3.1, R4.2, R5.1, R6.2, R16.2, R17.2, R19.2, R20.2, R22.2, R23.2, TP1.1, TP2.1, TP3.1, TP8.1, TP9.1, TP10.1, TP17.1, TP18.1, TP19.1, TP20.1, TP25.1, TP26.1, TP27.1, TP34.1, TP35.1, U1.3 (GND), U2.3 (GND), U3.3 (GND), U8.1, U8.3 (GND), U9.1, U9.3 (GND), U10.1, U10.3 (GND)
unnamed: C8.1, R15.1, R17.1, TP18.2, U8.2
unnamed: C9.1, R18.1, R19.1, TP19.2, U9.2
unnamed: C10.1, R21.1, R22.1, TP20.2, U10.2
unnamed: C1.1, D2.1 (K), R1.2, TP17.2, U1.2
unnamed: D3.2 (A), TP1.2, U1.4
unnamed: D3.1 (K), R2.1
unnamed: C2.1, D5.1 (K), R3.2, TP34.2, U2.2
unnamed: D6.2 (A), TP2.2, U2.4
unnamed: D6.1 (K), R4.1
unnamed: C3.1, D8.1 (K), R5.2, TP35.2, U3.2
unnamed: D9.2 (A), TP3.2, U3.4
unnamed: D9.1 (K), R6.1
unnamed: D22.1 (K), R20.1
unnamed: D23.1 (K), R23.1
unnamed: D24.1 (K), R16.1
unnamed: JP1.1 (A), U1.1
unnamed: JP2.1 (A), U2.1
unnamed: JP3.1 (A), U3.1
